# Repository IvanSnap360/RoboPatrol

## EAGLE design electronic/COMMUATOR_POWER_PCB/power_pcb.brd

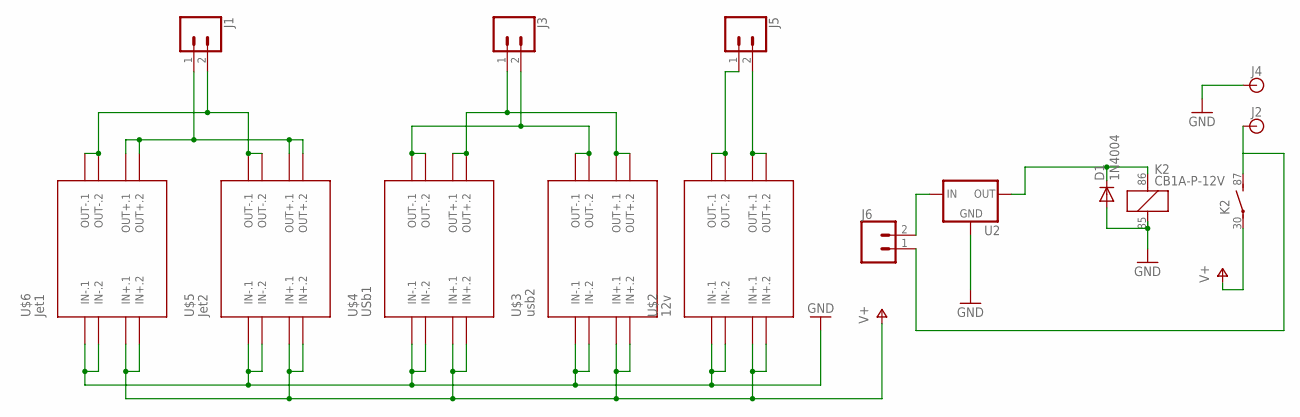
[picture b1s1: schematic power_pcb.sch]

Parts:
D1: 1N4004; DO41-10
J1, J3, J5, J6: CONN_025MM; SCREWTERMINAL-5MM-2
J2, J4: BANANA_CONN
K2: CB1A-P-12V; CB1
U2: V_REG_78XXSINK; TO220-IGO
U$2: 12v; DC-DC-STEP-DOWN-MP1584
U$3: usb2; DC-DC-STEP-DOWN-MP1584
U$4: USb1; DC-DC-STEP-DOWN-MP1584
U$5: Jet2; DC-DC-STEP-DOWN-MP1584
U$6: Jet1; DC-DC-STEP-DOWN-MP1584

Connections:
GND: D1.A, J4.P$1, K2.85 (2), U2.GND, U$2.IN-.1, U$2.IN-.2, U$3.IN-.1, U$3.IN-.2, U$4.IN-.1, U$4.IN-.2, U$5.IN-.1, U$5.IN-.2, U$6.IN-.1, U$6.IN-.2
unnamed: J2.P$1, J6.1, K2.87 (S)
unnamed: J1.1, U$5.OUT+.1, U$5.OUT+.2, U$6.OUT+.1, U$6.OUT+.2
unnamed: J1.2, U$5.OUT-.1, U$5.OUT-.2, U$6.OUT-.1, U$6.OUT-.2
unnamed: J3.2, U$3.OUT-.1, U$3.OUT-.2, U$4.OUT-.1, U$4.OUT-.2
unnamed: J3.1, U$3.OUT+.1, U$3.OUT+.2, U$4.OUT+.1, U$4.OUT+.2
unnamed: J5.1, U$2.OUT-.1, U$2.OUT-.2
unnamed: J5.2, U$2.OUT+.1, U$2.OUT+.2
unnamed: D1.C, K2.86 (1), U2.OUT
unnamed: J6.2, U2.IN
V+: K2.30, U$2.IN+.1, U$2.IN+.2, U$3.IN+.1, U$3.IN+.2, U$4.IN+.1, U$4.IN+.2, U$5.IN+.1, U$5.IN+.2, U$6.IN+.1, U$6.IN+.2

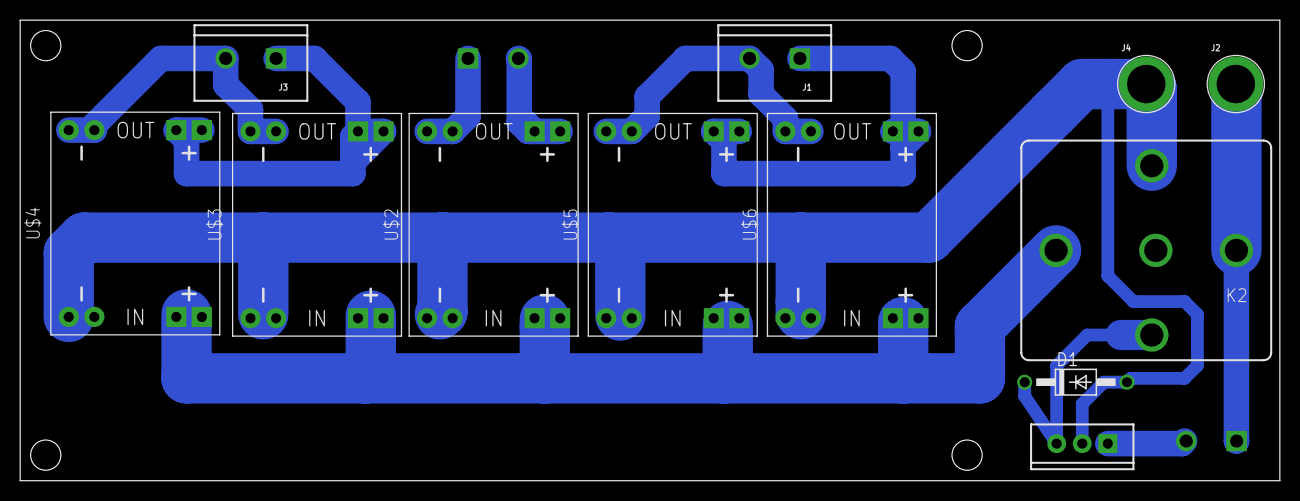
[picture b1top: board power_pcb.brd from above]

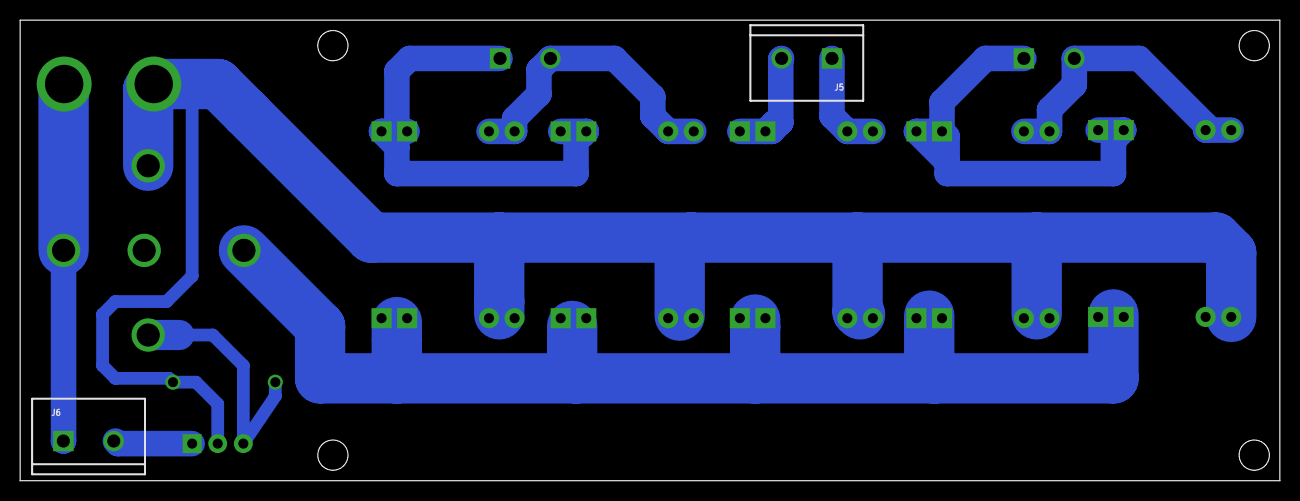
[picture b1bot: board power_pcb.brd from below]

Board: 2 copper layers, 125.0 x 45.7 mm, 14 parts (2 on the bottom side), 11 nets.

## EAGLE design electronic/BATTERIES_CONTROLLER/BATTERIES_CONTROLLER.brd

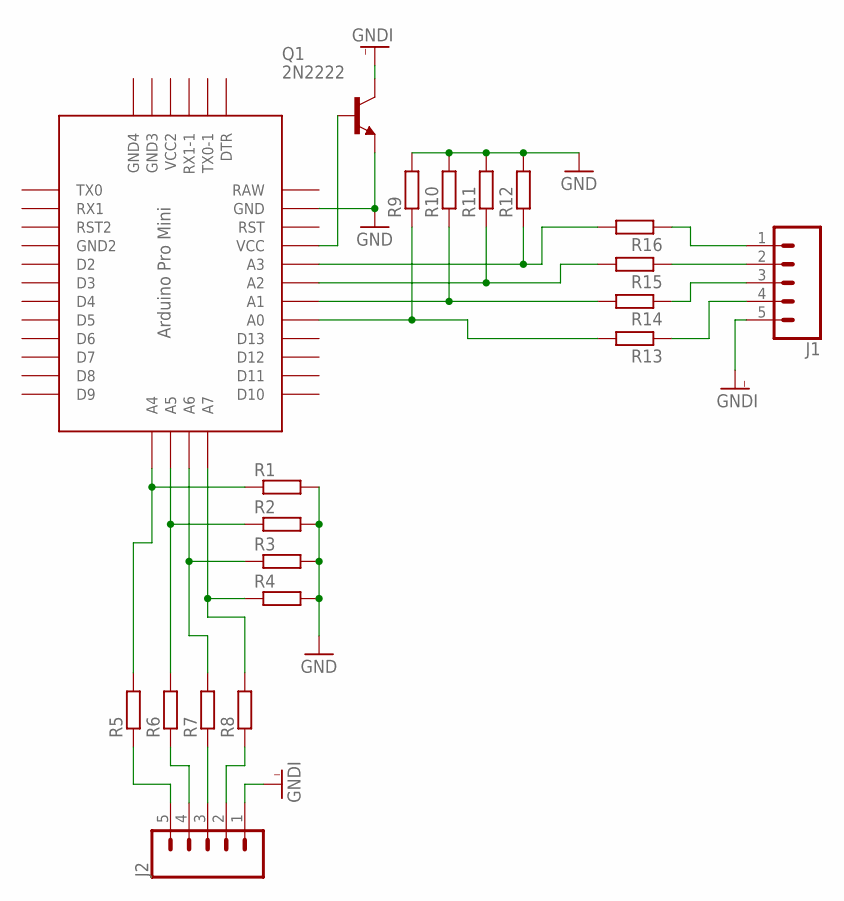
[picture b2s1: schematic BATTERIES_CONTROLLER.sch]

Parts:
J1, J2: CONN_05; 1X05
Q1: 2N2222; TO18
R1, R2, R3, R4, R5, R6, R7, R8, R9, R10, R11, R13, R14, R15, R16: R-EU_0204/7; 0204/7
R12: R-EU_0207/10; 0207/10
U$1: PRO-MINI

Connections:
GND: Q1.1 (E), R1.2, R2.2, R3.2, R4.2, R9.2, R10.2, R11.2, R12.2, U$1.GND
GNDI: J1.5, J2.1, Q1.3 (C)
unnamed: R1.1, R5.2, U$1.A4
unnamed: R2.1, R6.2, U$1.A5
unnamed: R3.1, R7.2, U$1.A6
unnamed: R4.1, R8.2, U$1.A7
unnamed: J2.5, R5.1
unnamed: J2.4, R6.1
unnamed: J2.3, R7.1
unnamed: J2.2, R8.1
unnamed: R9.1, R13.2, U$1.A0
unnamed: R10.1, R14.2, U$1.A1
unnamed: R11.1, R15.2, U$1.A2
unnamed: R12.1, R16.2, U$1.A3
unnamed: J1.4, R13.1
unnamed: J1.3, R14.1
unnamed: J1.2, R15.1
unnamed: J1.1, R16.1
unnamed: Q1.2 (B), U$1.VCC
RAW: U$1.RAW

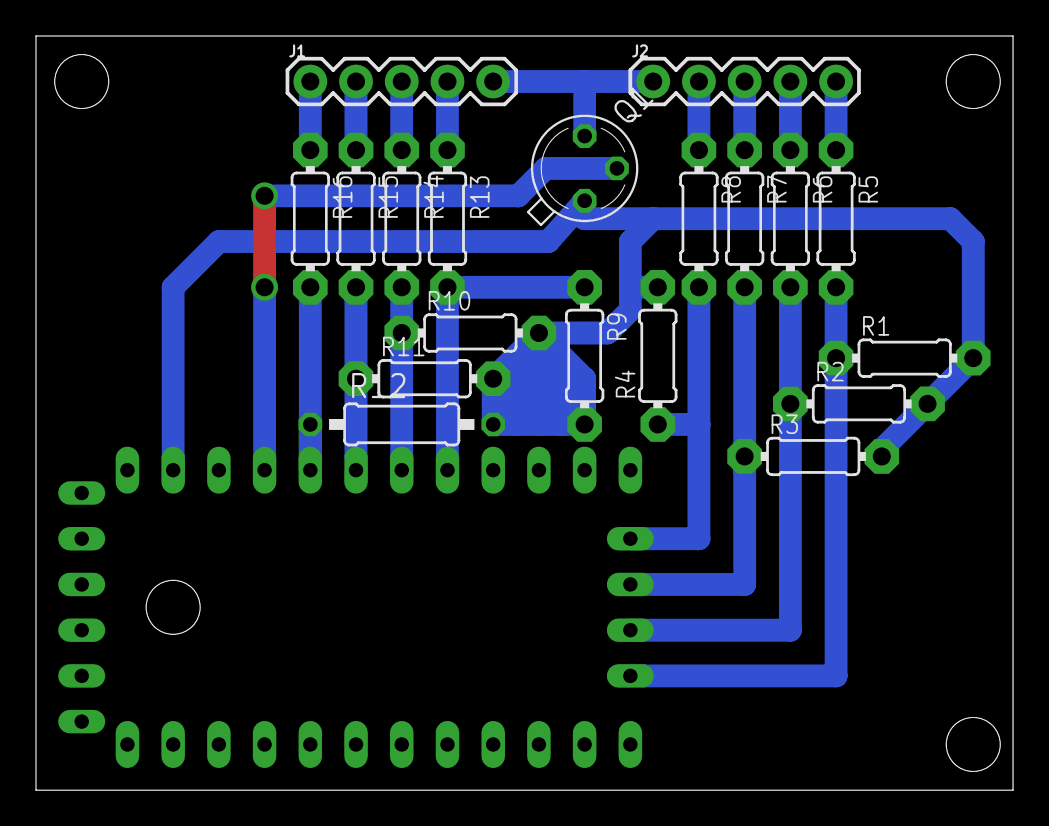
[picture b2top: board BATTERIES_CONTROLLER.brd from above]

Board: 2 copper layers, 54.3 x 41.9 mm, 20 parts (0 on the bottom side), 19 nets.

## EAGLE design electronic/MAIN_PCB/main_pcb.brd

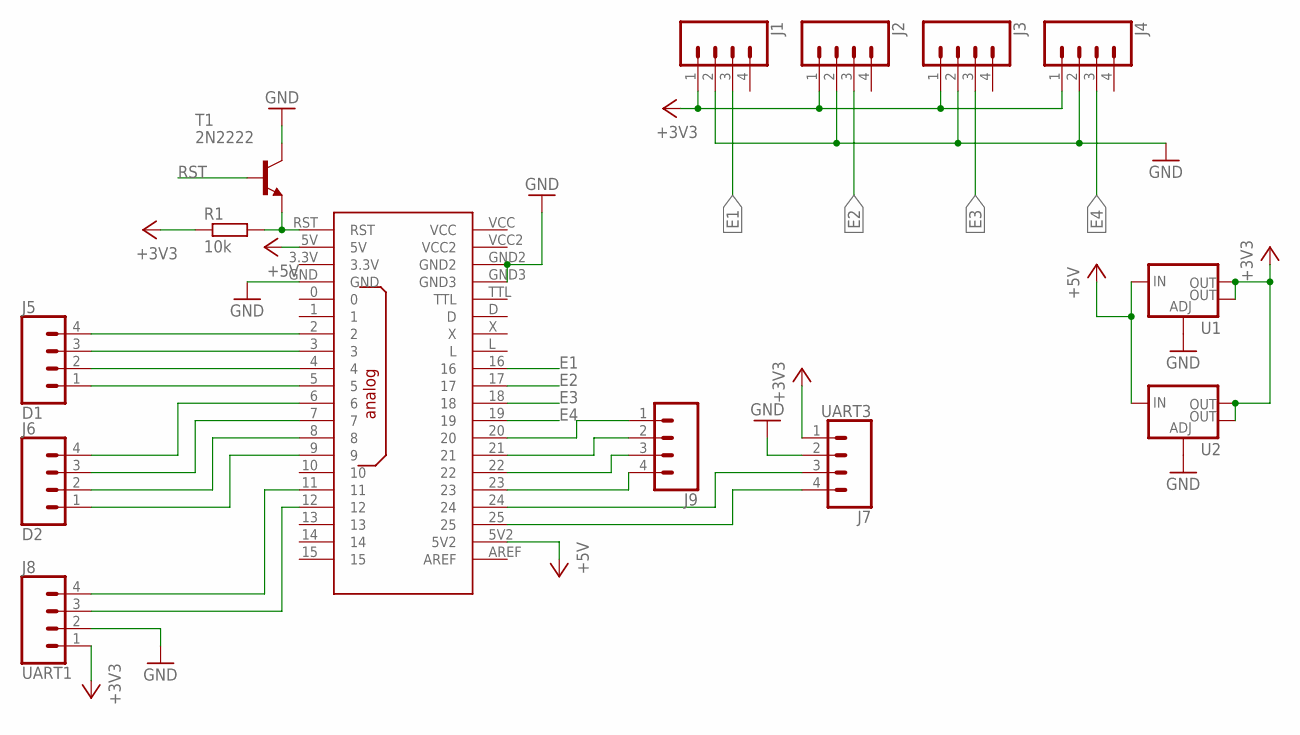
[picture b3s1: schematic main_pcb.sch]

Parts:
J1, J2, J3, J4: CONN_04POLAR; MOLEX-1X4
J5: D1; MOLEX-1X4
J6: D2; MOLEX-1X4
J7: UART3; 1X04
J8: UART1; 1X04
J9: CONN_04; 1X04
R1: 10k; 0204/7
T1: 2N2222; TO18
U1, U2: V_REG_LM1117SOT223; SOT223
U$1: OPENCM9.04

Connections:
+3V3: J1.1, J2.1, J3.1, J4.1, J7.1, J8.1, R1.1, U1.2 (OUT), U1.4 (OUT), U2.2 (OUT), U2.4 (OUT)
+5V: U1.3 (IN), U2.3 (IN), U$1.5V, U$1.5V2
E1: J1.3, U$1.16
E2: J2.3, U$1.17
E3: J3.3, U$1.18
E4: J4.3, U$1.19
GND: J1.2, J2.2, J3.2, J4.2, J7.2, J8.2, T1.3 (C), U1.1 (ADJ), U2.1 (ADJ), U$1.GND, U$1.GND2, U$1.GND3
unnamed: R1.2, T1.1 (E), U$1.RST
unnamed: J5.1, U$1.5
unnamed: J5.2, U$1.4
unnamed: J5.3, U$1.3
unnamed: J5.4, U$1.2
unnamed: J6.4, U$1.6
unnamed: J6.3, U$1.7
unnamed: J6.2, U$1.8
unnamed: J6.1, U$1.9
unnamed: J7.4, U$1.25
unnamed: J7.3, U$1.24
unnamed: J8.4, U$1.11
unnamed: J8.3, U$1.12
unnamed: J9.4, U$1.23
unnamed: J9.3, U$1.22
unnamed: J9.2, U$1.21
unnamed: J9.1, U$1.20
RST: T1.2 (B)

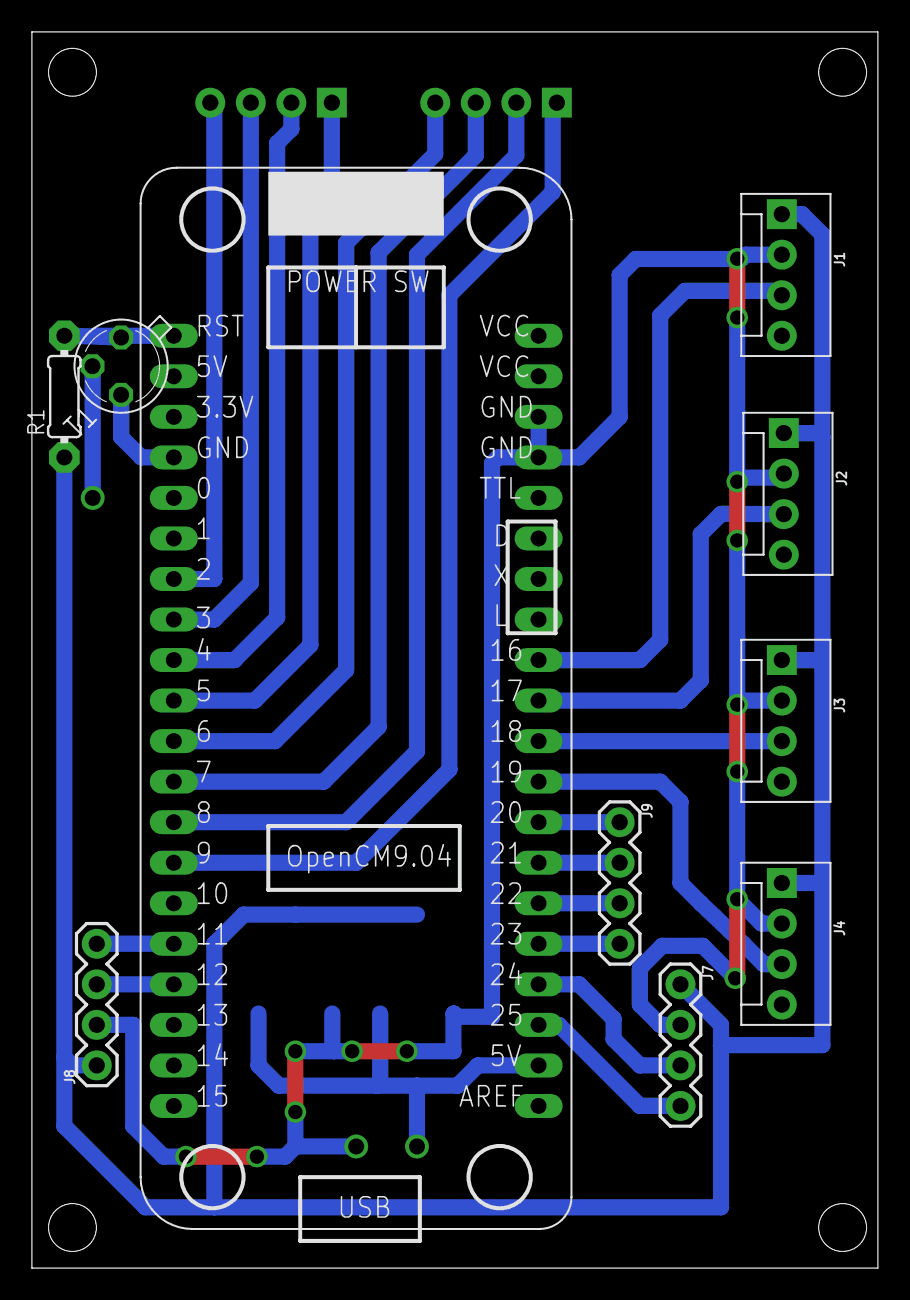
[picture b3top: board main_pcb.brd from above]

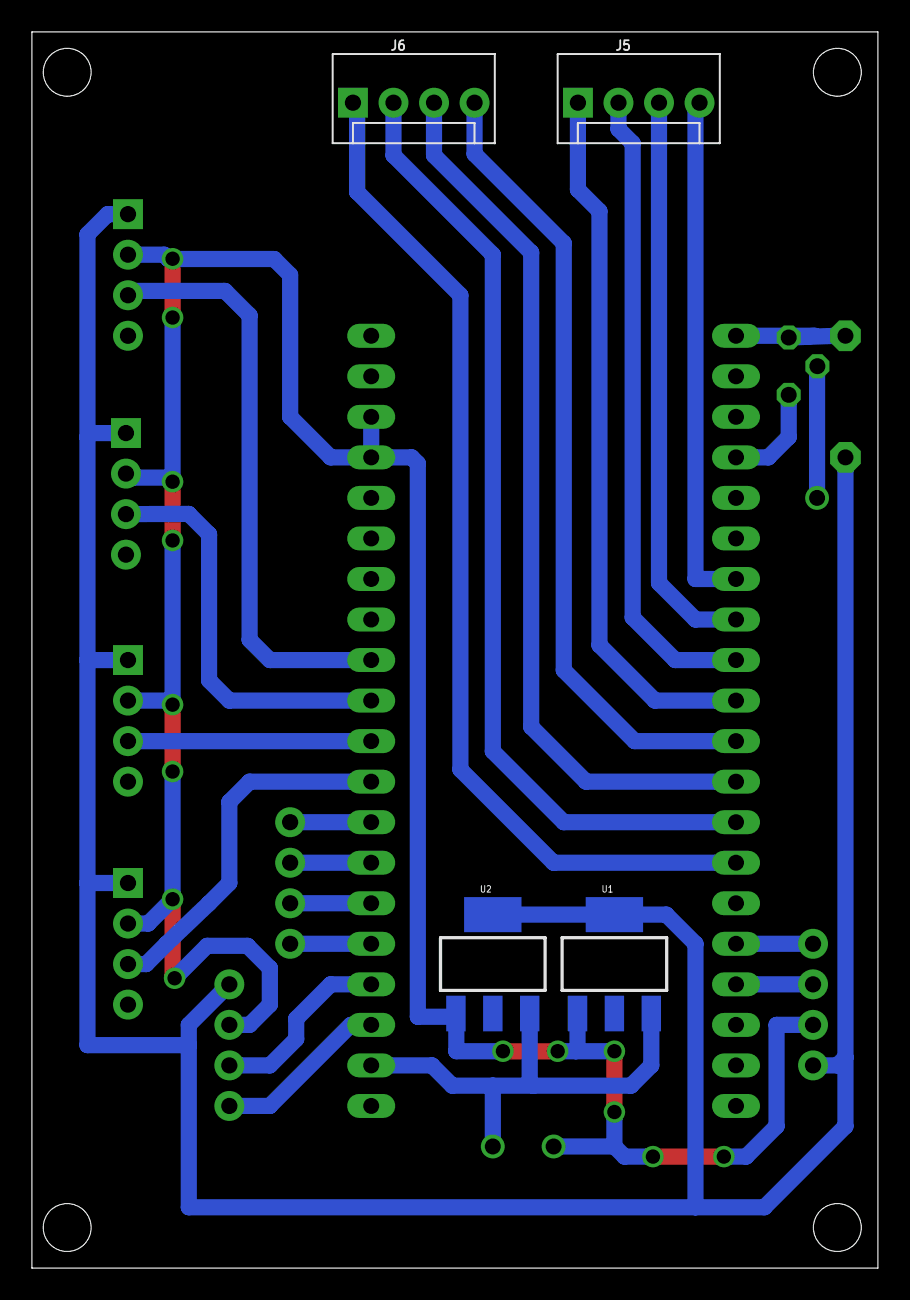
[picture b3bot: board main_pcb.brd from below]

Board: 2 copper layers, 53.0 x 77.5 mm, 14 parts (4 on the bottom side), 24 nets.

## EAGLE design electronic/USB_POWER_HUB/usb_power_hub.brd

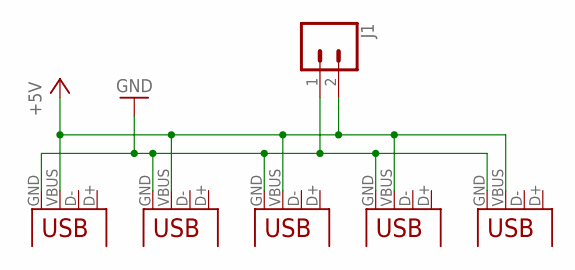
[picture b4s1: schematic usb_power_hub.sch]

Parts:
J1: CONN_025MM; SCREWTERMINAL-5MM-2
X1, X2, X3, X4, X5: USB-A-H

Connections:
+5V: J1.2, X1.VBUS, X2.VBUS, X3.VBUS, X4.VBUS, X5.VBUS
GND: J1.1, X1.GND, X2.GND, X3.GND, X4.GND, X5.GND

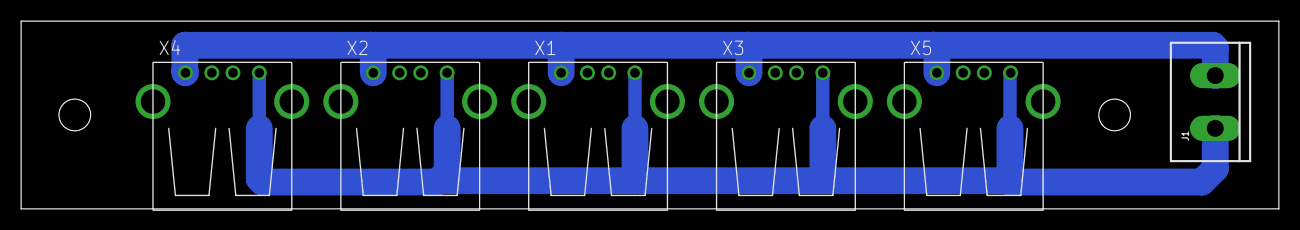
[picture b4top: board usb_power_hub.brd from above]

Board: 2 copper layers, 119.0 x 17.8 mm, 6 parts (0 on the bottom side), 2 nets.

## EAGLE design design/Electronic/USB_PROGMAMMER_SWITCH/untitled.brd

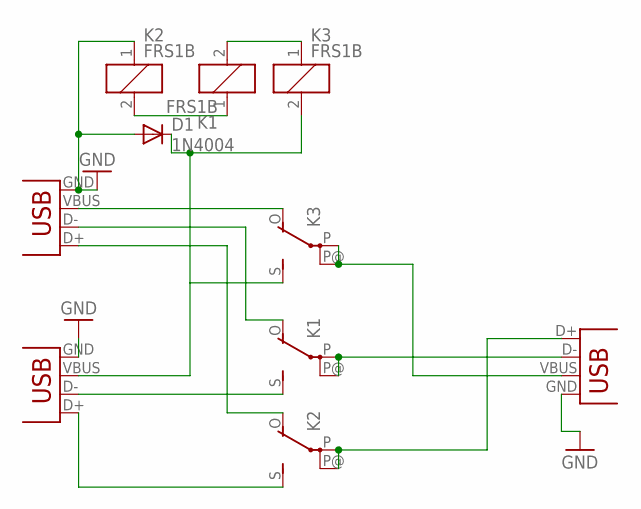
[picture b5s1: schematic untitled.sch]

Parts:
D1: 1N4004; DO41-10
K1, K2, K3: FRS1B
X1: USB-B-H
X2, X3: USB-A-H

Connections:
GND: D1.A, K2.1, X1.GND, X2.GND, X3.GND
unnamed: K3.P, K3.P@, X3.VBUS
unnamed: K1.P, K1.P@, X3.D-
unnamed: K1.S, X1.D-
unnamed: K2.P, K2.P@, X3.D+
unnamed: K2.S, X1.D+
unnamed: K2.O, X2.D+
unnamed: K1.O, X2.D-
unnamed: D1.C, K3.2, K3.S, X1.VBUS
unnamed: K3.O, X2.VBUS
unnamed: K1.1, K2.2
unnamed: K1.2, K3.1

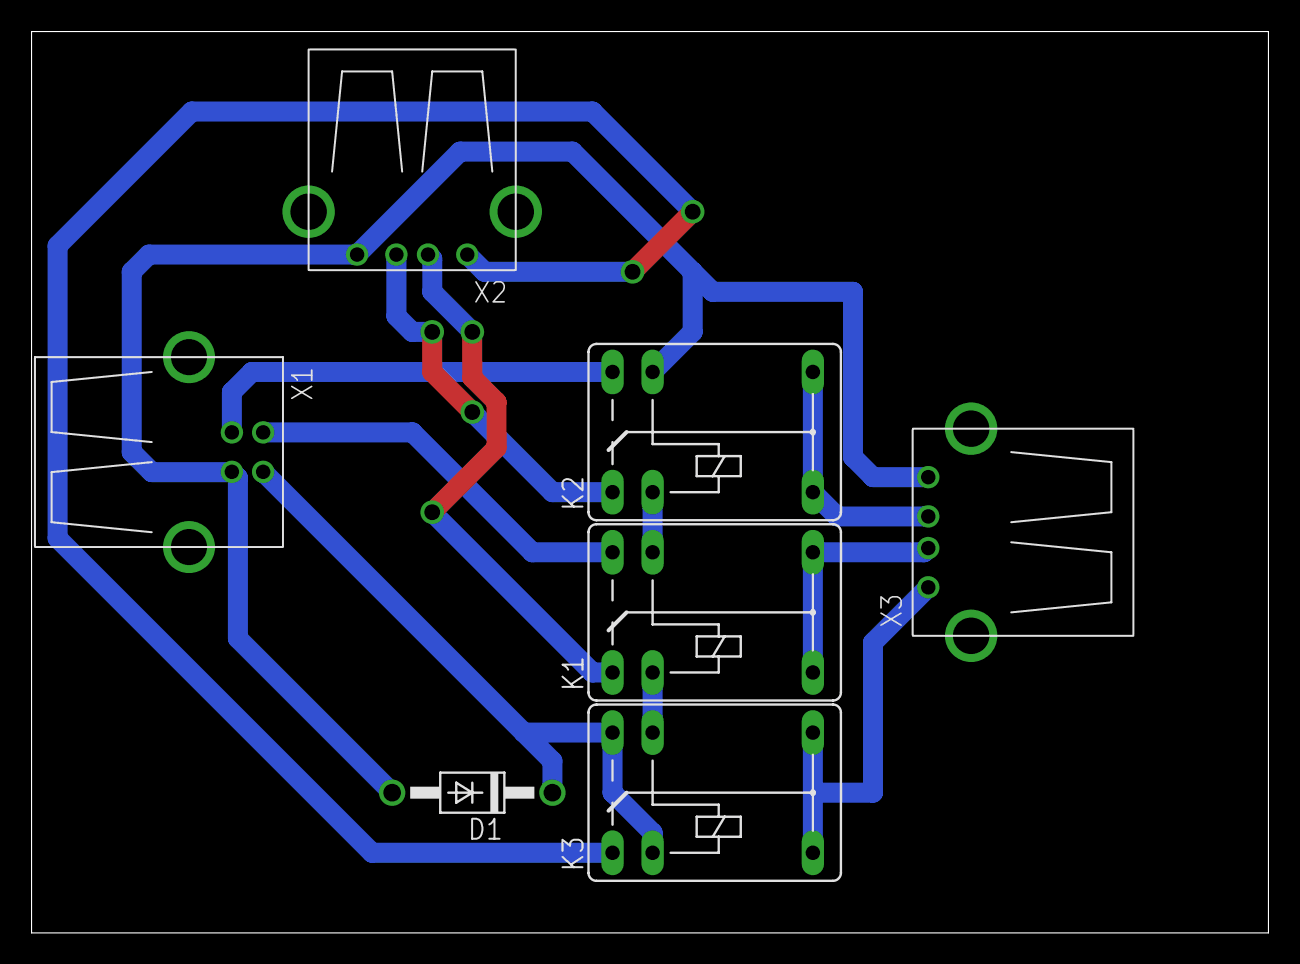
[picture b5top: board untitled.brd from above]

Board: 2 copper layers, 78.4 x 57.1 mm, 7 parts (0 on the bottom side), 12 nets.

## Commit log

2021-06-01 init2
2021-06-02 добавлены необходимые модели
2021-06-08 add realsense pkg and kml parser
2021-06-08 add scheme
2021-06-09 add test test platform
2021-06-11 add realsense files
2021-06-11 add manufacturing folder
2021-06-12 add draft model of dynamic pendant
    change ivan invetor 2019 to 2020
2021-06-13 change draft dynamic
2021-06-15 add relsenses plate V2
2021-06-19 add stm32cubemx project and ros_lib fo stm32f4xx
2021-06-21 test rama v2
2021-06-21 rama v3
2021-06-25 add rama v3
2021-06-25 add draft rama v4
2021-06-26 complete visual look box
2021-06-28 change realsenses plate
2021-07-01 fix repository
2021-07-01 fix repo2
2021-07-01 fix 3
2021-07-02 add fixfile 2
2021-07-02 fix deleting
2021-07-02 fix adding
2021-07-02 fix adding 2
2021-07-08 add imu firmware
2021-07-11 add 3d model, odometry
2021-07-12 fix some changes
2021-07-15 fix kinematic calc
2021-07-15 add teleop_pkg
2021-07-15 fix tf,change teleoo_pkg
2021-07-16 add tf for lidar
2021-07-16 add gmapping
2021-07-16 add slam_gmapping package
2021-07-17 add navigation
2021-07-17 fix commit
2021-07-17 add py_nodes converters
2021-07-17 odometry change
2021-07-17 change odom
2021-07-17 add start
2021-07-22 sysn commit
2021-07-22 syns commit 2
2021-07-23 syns commit 3
2021-07-23 syns commit 4
2021-07-23 change planner to dwa
2021-07-23 fix previos commit
2021-07-23 clear src
2021-07-23 change src
2021-07-23 fix packages
2021-07-23 syns commit
2021-07-28 fix gps, add pointcloud, fix realsense pkg
2021-07-30 change size
2021-07-31 change planner, no gps
2021-08-02 fix change
2021-08-03 summary
2021-08-05 add main pcb
2021-08-06 add power commutator
2021-08-07 add battery controller
2021-08-08 fix laptop add web app
2021-08-08 fix laptop2
2021-08-08 add desktop app
2021-08-08 web app working with ros
2021-08-10 Change GPS position
2021-08-12 add data frame
2021-08-12 save web_page java dependies
2021-08-15 add gps location tracking
2021-08-15 add video stream page
2021-08-16 some changes
2021-08-16 change battery holder
2021-08-17 change power pcb
2021-08-18 fix bugs
2021-08-18 change outside walls
2021-08-18 add lidar protection wall
2021-08-22 change program

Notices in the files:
parts and their libraries:
SparkFun-Connectors: Licensing: Creative Commons ShareAlike 4.0 International - https://creativecommons.org/licenses/by-sa/4.0
diy-modules: Released under the Creative Commons Attribution 4.0 International License: http://creativecommons.org/licenses/by/4.0
